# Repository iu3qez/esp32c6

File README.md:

# C6MacroSwitch

Interruttore/scene-controller Zigbee a batteria basato su ESP32-C6-WROOM-1-N8:
6 tasti meccanici Kailh Choc, LED di stato, alimentazione Li-ion 1S con LDO
very-low-dropout (XC6220B331), USB-C per programmazione via USB nativo,
charger MCP73831 predisposto ma non montato (DNP).

Progetto [Zener](https://github.com/diodeinc/pcb) (`pcb` CLI, richiede KiCad 10.x).

- Spec: `../docs/superpowers/specs/2026-06-11-c6-zigbee-macro-switch-design.md`
- Sourcing LCSC: `SOURCING.md`

## Comandi

```bash
pcb build C6MacroSwitch.zen    # valida il design
pcb layout C6MacroSwitch.zen   # sincronizza layout/C6MacroSwitch/layout.kicad_pcb
pcb open C6MacroSwitch.zen     # apre il layout in KiCad
pcb bom C6MacroSwitch.zen      # BOM con sourcing
```

Il round-trip KiCad 10 (salvataggio nativo → `pcb build`/`pcb layout`) è
verificato e funziona.

## Mappa GPIO

| GPIO | Funzione |
|---|---|
| IO0–IO5 | Tasti macro KEY1–KEY6 (LP-GPIO: wake da deep sleep, pull-up interni) |
| IO6 | ADC partitore batteria (1M/1M + 100nF) |
| IO8 | strapping, pullup 10k (download mode) |
| IO9 | Boot (pull-up 10k + tasto) |
| IO10 | LED di stato (verde, attivo alto) |
| IO12/IO13 | USB D−/D+ (USB nativo) |
| EN | Reset (pull-up 10k + 1µF + tasto) |

## Alimentazione

```
J_BAT (JST-PH) → Q_RVP/D_RVP (protezione inversione) → J_IMEAS (jumper misura corrente) → XC6220 → 3V3
USB VBUS → MCP73831 (DNP) → BAT+   |   USB VBUS → 1N5817W (DNP) → ingresso LDO
```

- Rimuovendo lo shunt da J_IMEAS si misura l'assorbimento totale a batteria.
- Protezione inversione batteria: montare ESATTAMENTE UNO tra Q_RVP
  (AO3401A, basse perdite) e D_RVP (1N5817W, semplice, ~300 mV di caduta);
  mai entrambi.
- D_USB_PWR (DNP) permette flash/test da USB senza batteria.
  **Attenzione:** mai montarlo con batteria collegata e jumper J_IMEAS
  inserito (bypassa il charger).
- Charger e relativi R/LED tutti DNP sulle prime board.
- Cutoff batteria firmware consigliato ~3,4 V (sotto, il rail esce di
  regolazione durante i burst TX).

## Note di popolamento

- SW1–SW6 (Kailh Choc CPG135001D01): esauriti su LCSC, montaggio in proprio.
- Tutti i passivi 0603

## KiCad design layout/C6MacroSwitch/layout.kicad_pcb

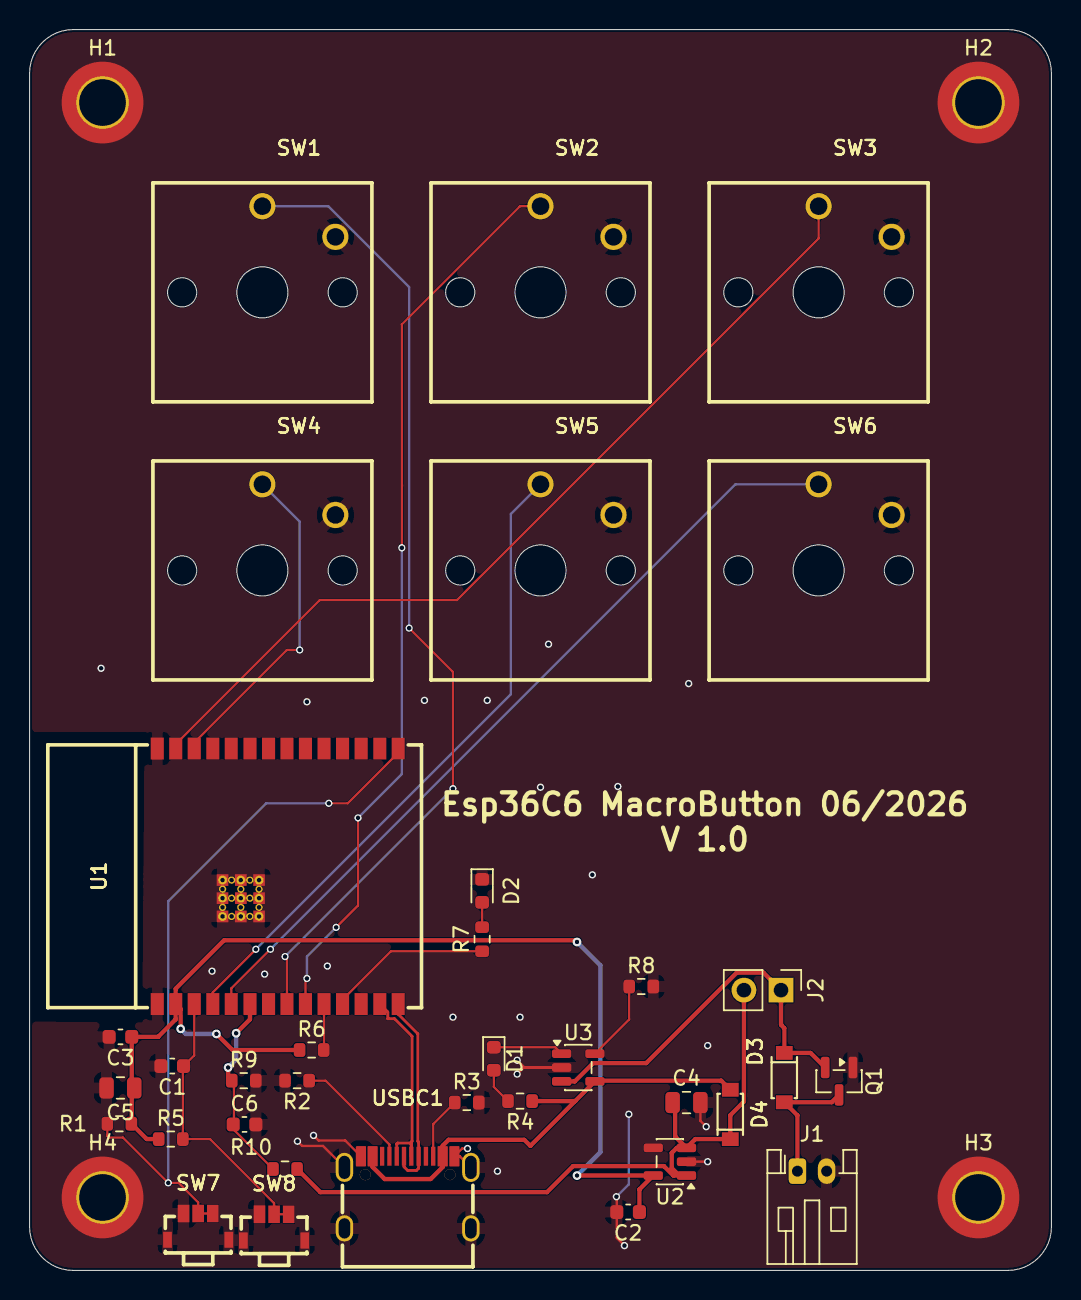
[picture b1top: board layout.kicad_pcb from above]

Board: 2 copper layers, 70.0 x 85.0 mm, 39 parts (0 on the bottom side), 25 nets.

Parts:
C1: GCM188R71E105KA64D; C_0603_1608Metric
C2: GRM188Z71A106KA73D; C_0603_1608Metric
C3, C6: GRM188R72A104KA35D; C_0603_1608Metric
C4, C5: GRM21BZ71E106KE15K; C_0805_2012Metric
D1: LED RED; LED_0603_1608Metric
D2: LED GREEN; LED_0603_1608Metric
D3, D4: 1N5817W; SOD-123_L2.7-W1.6-LS3.6-RD
H1, H2, H3, H4: M3 DIN965 TopBottom; MountingHole_3.2mm_M3_DIN965_Pad_TopBottom
J1: S2B-PH-K-S(LF)(SN); JST_PH_S2B-PH-K_1x02_P2.00mm_Horizontal
J2: 61300211121; PinHeader_1x02_P2.54mm_Vertical
Q1: AO3401A; SOT-23
R1, R5, R6: ERJ-3EKF1002V; R_0603_1608Metric
R2, R3: ERJ-3EKF5101V; R_0603_1608Metric
R4, R7: ERJ-3EKF1001V; R_0603_1608Metric
R8: ERJ-3EKF2001V; R_0603_1608Metric
R9, R10: ERJ-3EKF1004V; R_0603_1608Metric
SW1, SW2, SW3, SW4, SW5, SW6: CPG135001D01; KEY-TH_CPG135001D0X
SW7, SW8: TSA061B2808B; SW-SMD_TSA061B2808B
U1: ESP32-C6-WROOM-1-N8; WIRELM-SMD_ESP32-C6-WROOM-1
U2: XC6220B331MR-G; SOT-23-5
U3: MCP73831T-2ACI/OT; SOT-23-5
USBC1: TYPE-C-31-M-12; USB-C_SMD-TYPE-C-31-M-12_1

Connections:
3V3: C2.1, C3.1, C5.1, R1.1, R5.1, R6.1, U1.2, U2.5
BAT_RAW: D3.2, J1.1, Q1.3
BOOT: R1.2, SW7.1, SW7.2, U1.15
CC1: R2.1, USBC1.A5
CC2: R3.1, USBC1.B5
CHG_LED_A: D1.2, R4.2
CHG_PROG: R8.1, U3.5
CHG_STAT: D1.1, U3.1
EN: C1.1, R5.2, SW8.1, SW8.2, U1.3
GND: C1.2, C2.2, C3.2, C4.2, C5.2, C6.2, D2.1, H1.1, H2.1, H3.1, H4.1, J1.2, Q1.1, R2.2, R3.2, R8.2, R9.2, SW1.2, SW2.2, SW3.2, SW4.2, SW5.2, SW6.2, SW7.3, SW7.4, SW7.5, SW8.3, SW8.4, SW8.5, U1.1, U1.28, U1.29, U1.30, U1.31, U1.32, U1.33, U1.34, U1.35, U1.36, U1.37, U2.2, U3.2, USBC1.1, USBC1.2, USBC1.3, USBC1.4, USBC1.A1B12, USBC1.B1A12
IO8_STRAP: R6.2, U1.10
KEY1: SW1.1, U1.8
KEY2: SW2.1, U1.9
KEY3: SW3.1, U1.27
KEY4: SW4.1, U1.26
KEY5: SW5.1, U1.4
KEY6: SW6.1, U1.5
LED: R7.1, U1.11
LED_A: D2.2, R7.2
USB_D_N: U1.13, USBC1.A7, USBC1.B7
USB_D_P: U1.14, USBC1.A6, USBC1.B6
VBAT: D3.1, J2.1, Q1.2, U3.3
VBAT_SENSE: C6.1, R9.1, R10.2, U1.6
VBAT_SW: C4.1, D4.1, J2.2, R10.1, U2.1, U2.3
VBUS: D4.2, R4.1, U3.4, USBC1.A4B9, USBC1.B4A9

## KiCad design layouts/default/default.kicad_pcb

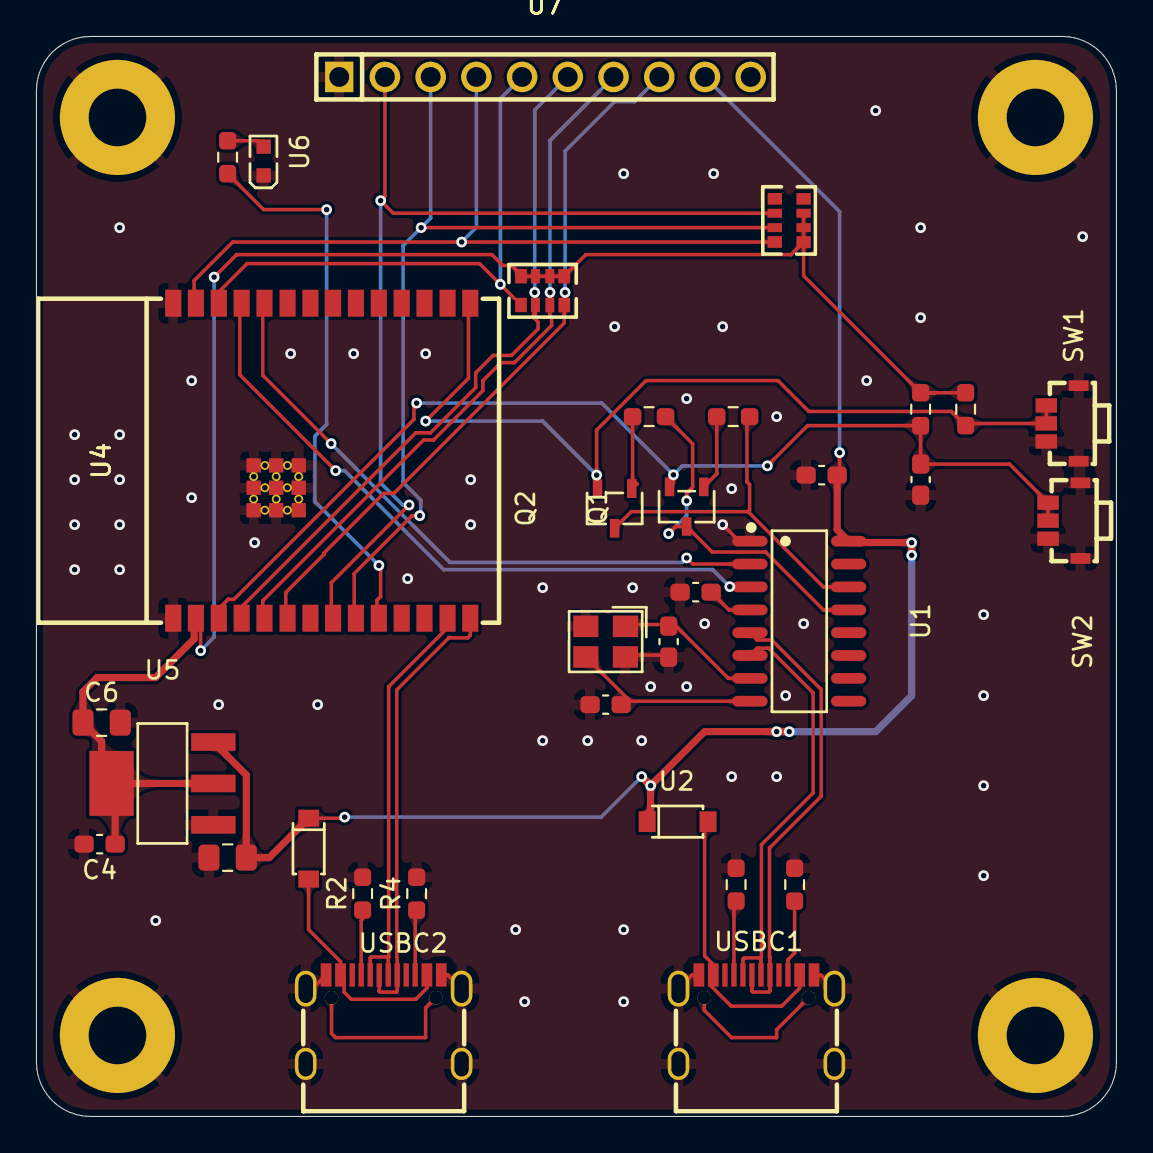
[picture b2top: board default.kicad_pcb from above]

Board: 2 copper layers, 60.0 x 60.0 mm, 37 parts (0 on the bottom side), 33 nets.

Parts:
C1, C2, C4: 100nF ±10% 50V X7R; C0603
C3: 1µF ±10% 50V X5R; C0603
C5: 10µF ±10% 25V X5R; C0805
C6: 22µF ±20% 25V X5R; C0805
C7, C8: 22pF ±5% 50V C0G; C0603
H1, H2, H3, H4: MountingHole_3.2_M3_Pad
Q1, Q2: SOT-23-3_L3.0-W1.7-P0.95-LS2.9-BR
R1, R2, R3, R4: 5.1kΩ ±1% 100mW; R0603
R5, R7, R15, R16: 10kΩ ±1% 100mW; R0603
R6: 1kΩ ±1% 100mW; R0603
RN1, RN2: RES-ARRAY-SMD_0603-8P-L3.2-W1.6-BL
SW1, SW2: SW-SMD_TSA061B2808B
U1: SOIC-16_L9.9-W3.9-P1.27-LS6.0-BL
U2, U3: SOD-123_L2.7-W1.6-LS3.6-RD
U4: WIRELM-SMD_ESP32-C6-WROOM-1
U5: SOT-223-4_L6.5-W3.5-P2.30-LS7.0-BR
U6: LED0603-RD_GREEN
U7: HDR-TH_10P-P2.54-V-M-1
USBC1, USBC2: USB-C_SMD-TYPE-C-31-M-12_1
X1: CRYSTAL-SMD_4P-L3.2-W2.5-BL

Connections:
A: R6.2, U6.2
GND: C1.2, C2.2, C3.2, C4.2, C5.2, C6.2, C7.2, C8.2, H1.1, H2.1, H3.1, H4.1, R1.2, R2.2, R3.2, R4.2, SW1.3, SW1.4, SW1.5, SW2.3, SW2.4, SW2.5, U1.1, U4.1, U4.28, U4.29, U4.30, U4.31, U4.32, U4.33, U4.34, U4.35, U4.36, U4.37, U5.1, U6.1, U7.1, USBC1.1, USBC1.2, USBC1.3, USBC1.4, USBC1.A1B12, USBC1.B1A12, USBC2.1, USBC2.2, USBC2.3, USBC2.4, USBC2.A1B12, USBC2.B1A12, X1.2, X1.4
IO0: RN2.6, U4.8, U7.2
IO1: RN2.7, U4.9, U7.3
IO2: RN2.8, U4.27, U7.4
IO3: RN1.5, U4.26, U7.5
IO4: RN1.6, U4.4, U7.6
IO5: RN1.7, U4.5, U7.7
IO6: RN1.8, U4.6, U7.8
IO8: R6.1, U4.10
RXD: U1.3, U4.25
TXD: U1.2, U4.24
V3: C1.1, U1.4
XI: C7.1, U1.7, X1.1
XO: C8.1, U1.8, X1.3
boot_pullup-E: Q2.2, R7.2, SW1.1, SW1.2, U4.15
btn_reset-E: C3.1, Q1.2, R5.2, SW2.1, SW2.2, U4.3
cc1_r_debug-A5: R1.1, USBC1.A5
cc1_r_esp-A5: R2.1, USBC2.A5
cc2_r_debug-B5: R3.1, USBC1.B5
cc2_r_esp-B5: R4.1, USBC2.B5
ch340g-C-0: Q1.3, R16.1, U1.13
ch340g-C-1: Q2.3, R15.1, U1.14
ch340g-D_N: U1.6, USBC1.A7, USBC1.B7
ch340g-D_P: U1.5, USBC1.A6, USBC1.B6
diode_debug-VBUS: U2.2, USBC1.A4B9, USBC1.B4A9
diode_esp-VBUS: U3.2, USBC2.A4B9, USBC2.B4A9
esp32-D_N: U4.13, USBC2.A7, USBC2.B7
esp32-D_P: U4.14, USBC2.A6, USBC2.B6
footprint-B-0: Q1.1, R15.2
footprint-B-1: Q2.1, R16.2
power_3v3-VCC: C4.1, C6.1, R5.1, R7.1, RN1.1, RN1.2, RN1.3, RN1.4, RN2.1, RN2.2, RN2.3, U4.2, U5.2, U5.4
power_5v-VCC: C2.1, C5.1, U1.16, U2.1, U3.1, U5.3, U7.9

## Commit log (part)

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2026-02-17 wip: ESP32-C6 dev board schematic and parts
    Full schematic: USB-C x2, AMS1117-3.3 LDO, CH340G debug UART,
    12MHz crystal, GPIO header, buttons, LED, mounting holes.
    Auto-picked passives (0603/0805). Mounting holes WIP (needs ato 0.14+).
2026-02-17 Upgrade to atopile 0.14 and use official mounting-holes package
    - Bump requires-atopile to ^0.14.0, mounting-holes dep to 0.2.0
    - Switch from local MountingHole_M3 workaround to official package
    - Remove local parts/MountingHole_3_2_M3_Pad (now from package)
    - Add S8050 NPN transistor part for upcoming auto-reset circuit
    - Parts updated by atopile 0.14 build (traits, symbols, footprints)
2026-02-17 Add additional ignore patterns for project files
2026-02-17 Add MountingHole part library to fp-lib-table
2026-02-17 Add Changjiang S8050 transistors and auto-reset circuit to schematic
2026-02-17 board layout
2026-02-18 Replace ESP32-C6-MINI-1 footprint and 3D models
2026-02-18 Update PCB and passive footprints from ato build
2026-02-18 Replace 7 GPIO pullup resistors with two C29718 resistor arrays
2026-02-19 Name USB signals with _P/_N suffixes for KiCad differential pair routing
    Rename USB-C connector D+/D- signals (DP1/DN1 → D_P/D_N) and CH340G
    signals (UDpos/UDneg → UD_P/UD_N) so KiCad auto-detects both USB
    differential pairs (esp32-D_P/N and ch340g-D_P/N).
    Also reorder RN1/RN2 pullup array GPIO assignments so pin order
    descends left-to-right matching the header physical layout.
2026-02-19 Layout quasi ok.
2026-02-19 Readme
2026-02-26 New footprint for C6
2026-02-26 Cleanupy
2026-04-19 Keyboard ATO
2026-04-19 Mssing parts
2026-04-19 Modded kicad files
2026-06-11 chore: install diodeinc/pcb agent skills
2026-06-11 docs: add design spec for C6 Zigbee macro switch (Zener variant)
2026-06-11 docs: rewrite CLAUDE.md for Zener toolchain pivot
2026-06-11 docs: macro keys are Kailh Choc CPG135001D01 mechanical switches
2026-06-11 docs: implementation plan for C6 Zigbee macro switch (Zener)
2026-06-11 feat(zener): scaffold pcb workspace for C6MacroSwitch
2026-06-11 feat(zener): ESP32-C6-WROOM-1-N8 component (reused verified sym/fp)
2026-06-11 feat(zener): Kailh Choc CPG135001D01 switch component
2026-06-11 feat(zener): TYPE-C-31-M-12 USB-C connector component
2026-06-11 feat(zener): tactile button and 1N5817W Schottky components
2026-06-11 feat(zener): XC6220 LDO, MCP73831 charger and JST-PH battery connector
2026-06-11 docs(zener): LCSC sourcing table with stock verification
2026-06-11 feat(zener): complete C6MacroSwitch top-level wiring
2026-06-11 refactor(zener): uppercase USB interface name per naming convention
2026-06-11 feat(zener): KiCad 10 round-trip verified (pcbnew resave + layout resync)
2026-06-11 docs(zener): board README with GPIO map and power architecture
2026-06-12 refactor(zener): promuovi il progetto Zener a root del repo
    Rimosso il vecchio progetto atopile (main.ato, keypad.ato, ato.yaml,
    parts/, layouts/, tmp/) e spostato il workspace Zener da zener/ alla
    root: C6MacroSwitch.zen, components/, layout/, pcb.toml diventano
    top-level. Adottati README e .gitignore (KiCad) di Zener.
    atopile resta recuperabile da git history; la migrazione è motivata
    da atopile <=0.15.7 che non rilegge i PCB salvati da KiCad 10.
2026-06-12 fix(zener): porta i LED a 0603 e fissa il vincolo package
    I due LED (D_CHG, D_LED) erano gli unici footprint 0402, fuori dalla
    specifica hardware. Portati a 0603 come R e C. CLAUDE.md aggiornato:
    resistenze, condensatori e LED in 0603 o più grande, mai 0402.
2026-06-12 docs(zener): LED 0603 in casa, nessun MPN richiesto
    I LED sono generici 0603 già disponibili: come il modulo ESP32 non
    serve un part number. Documentato in CLAUDE.md e con un commento sul
    design che il warning di build "No house LED found ... 0603" è atteso.
2026-06-12 feat(zener): resync layout KiCad ai LED 0603
    Rigenerato il .kicad_pcb dopo il cambio package dei LED: i footprint
    D_CHG/D_LED passano da LED_0402_1005Metric a LED_0603_1608Metric,
    piazzamento preservato. Allinea il layout al design.
2026-06-12 feat(zener): piazza i 6 Choc su griglia 1u 2x3 (pitch 19.05mm)
    Switch macro disposti su griglia 2x3 a pitch MX 1u (19.05mm) con stessa
    rotazione; origine footprint compensata per l'offset del polo centrale
    (-2.5,+4.85) così i centri keycap cadono su coordinate pulite. Nessuna
    collisione Choc-Choc.
    WIP floorplan: il cluster si sovrappone al supporto (ESP32/passivi),
    da riposizionare sotto i tasti nella fase di layout finale.
2026-06-12 feat(zener): primo sbroglio e layout della board
    Prima passata di routing manuale in KiCad: 151 tracce, 17 via e 3 zone
    di rame, con relative net class e impostazioni di progetto.
2026-06-12 fix(zener): review fixes — LDO caps 10uF, reverse-battery Q/D options, IO8 strap pullup, LED to IO10, Choc NPTH+courtyard
2026-06-12 fix(zener): LDO caps to 0805 for DC-bias derating margin
2026-06-13 feat(zener): 4x M3 corner mounting holes (GND) + 3mm rounded board corners
2026-06-13 feat(zener): ulteriore sbroglio e layout della board
2026-06-13 fix(zener): thermal vias on ESP32-C6 EP pads (fixes isolated GND pad 33, improves RF ground)
2026-06-23 Update passive component note in README
